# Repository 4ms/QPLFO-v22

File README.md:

#QPLFO v2.2
(also known as QPLFO v3)

This code runs on the STM32F030 version of the QPLFO, which is the factory-assembled version after March 2016. This code will not work on any kit versions of the QPLFO, nor any PCBs labeled version 1.x (green PCBs).

Note that one of the SWD programming pins is also used for the UI, so once the code has been flashed, it is difficult to re-flash it. The best technique I've found is to hit the reset button on the PCB at the right moment just before flashing.

This project was began using the [STM32F030x4 Application Template] (https://github.com/MrSpock/stm32f030x-gcc-template) from Martin Jurczuk, which is highly based on Mike Szczys [STM32F0-DISCOVERY template] (https://github.com/szczys/stm32f0-discovery-basic-template)

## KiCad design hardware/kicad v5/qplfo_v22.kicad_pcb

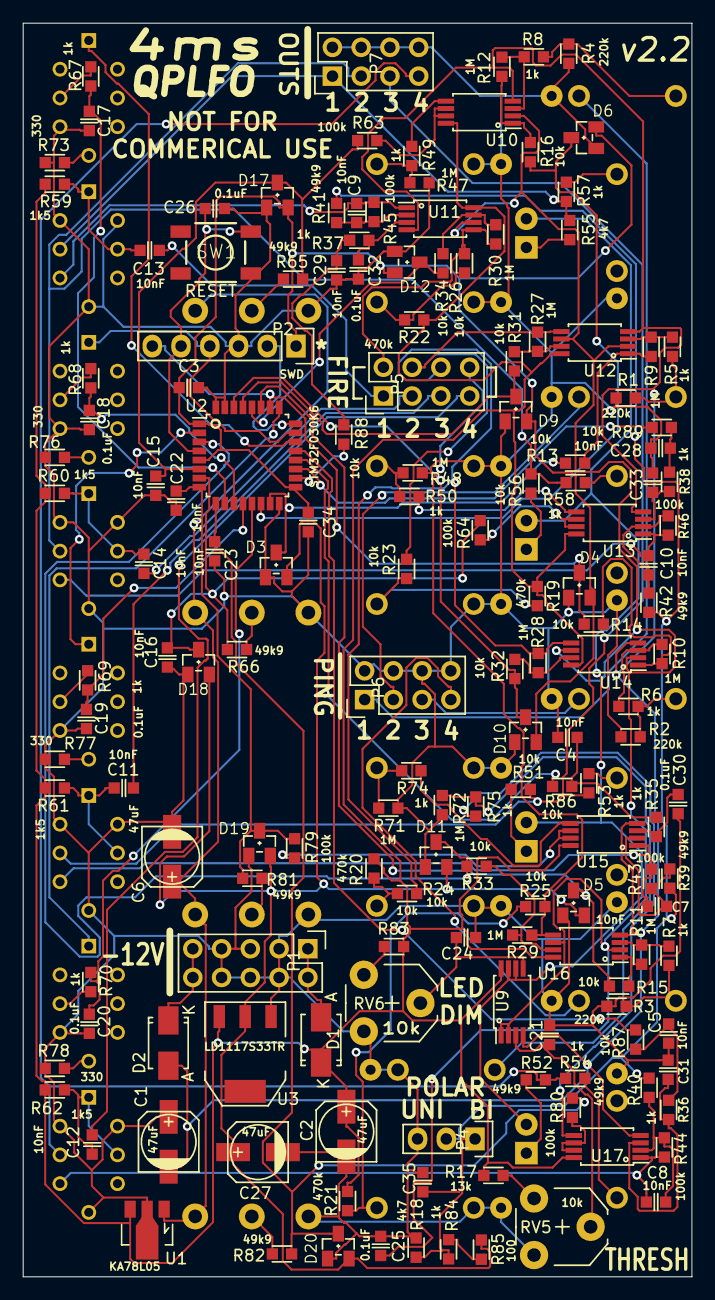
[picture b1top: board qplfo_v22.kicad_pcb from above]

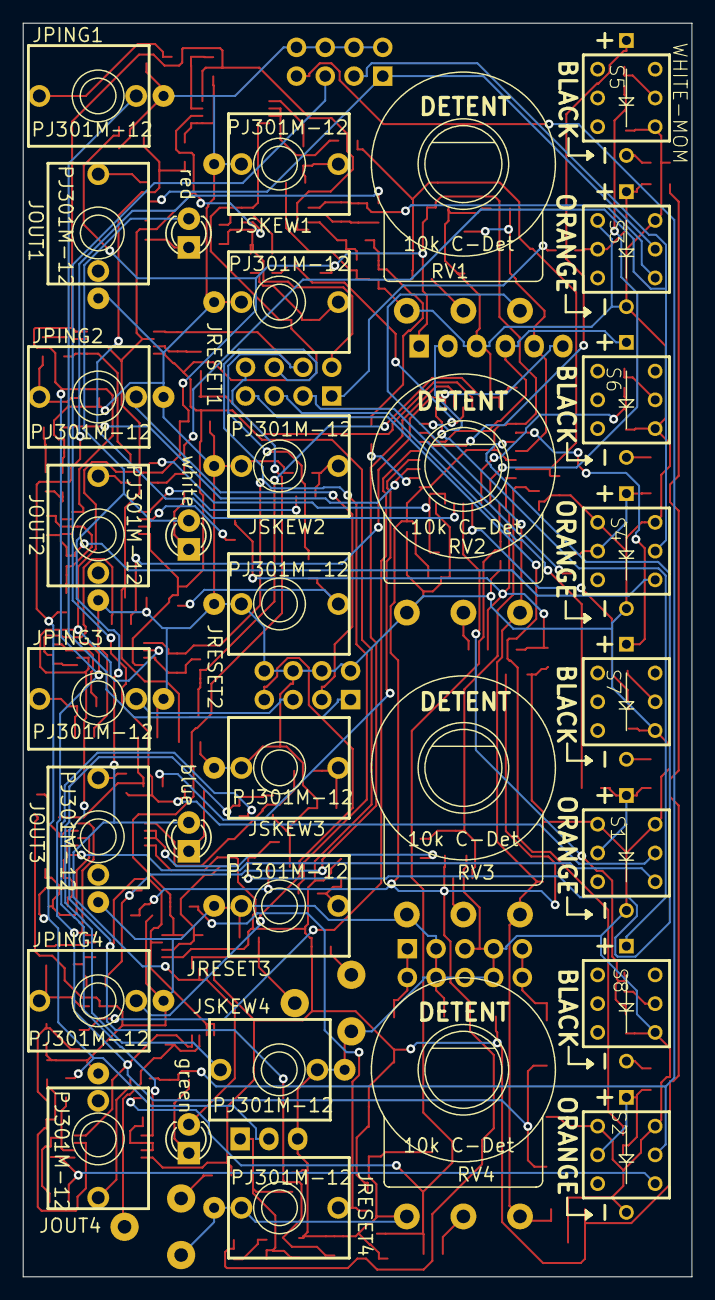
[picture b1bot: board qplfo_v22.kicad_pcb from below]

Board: 2 copper layers, 59.1 x 110.7 mm, 191 parts (32 on the bottom side), 130 nets.

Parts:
C1, C2, C6, C27: 47uF; c_elec_5x5.3
C3, C17, C18, C19, C20, C21, C24, C25, C26, C30, C31, C32, C33, C34, C35: 0.1uF; C0603
C4, C5, C7, C8, C9, C10, C11, C12, C13, C14, C15, C16, C22, C23, C28, C29: 10nF; C0603
D1, D2: B140; Diode-SMA_Standard
D3, D4, D5, D6, D9, D10, D11, D12, D17, D18, D19, D20: BAT54S; SOT23
D13: blue; LED-3MM-SQUARE-ANODE
D14: green; LED-3MM-SQUARE-ANODE
D15: red; LED-3MM-SQUARE-ANODE
D16: white; LED-3MM-SQUARE-ANODE
JOUT1, JOUT2, JOUT3, JOUT4: PJ301M-12; PJ301M-12-FIX
JPING1, JPING2, JPING3, JPING4: PJ301M-12; PJ301M-12-FIX
JRESET1, JRESET2, JRESET3, JRESET4: PJ301M-12; PJ301M-12-FIX
JSKEW1, JSKEW2, JSKEW3, JSKEW4: PJ301M-12; PJ301M-12-FIX
P1: CONN_02X05; Pin_Header_Straight_2x05
P2: SWD; Pin_Header_Straight_1x06
P4: HEADER-MALE-1X3-TH; Pin_Header_Straight_1x03
P5: FIRE; Pin_Header_Straight_2x04
P6: PINGS; Pin_Header_Straight_2x04
P7: OUTS; Pin_Header_Straight_2x04
R1, R2, R3, R4: 220k; R0603
R5, R6, R7, R8, R35, R36, R37, R38, R49, R50, R53, R54, R57, R58, R67, R68, R69, R70, R74, R75, R84: 1k; R0603
R9, R10, R11, R12, R27, R28, R29, R30, R47, R48, R71, R72: 1M; R0603
R13, R14, R15, R16, R23, R24, R25, R26, R31, R32, R33, R34, R51, R56, R83, R86, R87, R88, R89: 10k; R0603
R17: 13k; R0603
R18, R55: 4k7; R0603
R19, R20, R21, R22: 470k; R0603
R39, R40, R41, R42, R52, R65, R66, R81, R82: 49k9; R0603
R43, R44, R45, R46, R63, R64, R79, R80: 100k; R0603
R59, R60, R61, R62: 1k5; R0603
R73, R76, R77, R78: 330; R0603
R85: 100; R0603
RV1, RV2, RV3, RV4: 10k C-Det; 16MM-RV16AF-4A
RV5, RV6: 10k; Potentiometer_VishaySpectrol-Econtrim-Type36M
S1, S2, S3, S4: ORANGE-LAT; BUTTON-LED-PB61303
S5, S6, S7, S8: WHITE-MOM; BUTTON-LED-PB61303
SW1: RESET; BUTTON-TACT-SKQG
U1: KA78L05; SOT89-3_Housing
U2: STM32F030K6; LQFP-32_7x7mm_Pitch0.8mm
U3: LD1117S33TR; SOT-223
U9, U10, U11, U12, U13, U14, U15, U16, U17: TL082; TSSOP-8_4.4x3mm_Pitch0.65mm

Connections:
+3V3: C3.1, C27.1, C34.1, D3.2, D4.2, D5.2, D6.2, D9.2, D10.2, D11.2, D12.2, D17.2, D18.2, D19.2, D20.2, P2.1, R85.2, U2.1, U2.5, U2.17, U3.2
+12V: C2.1, D1.1, R17.2, R19.2, R20.2, R21.2, R22.2, R59.1, R60.1, R61.1, R62.1, R83.2, U1.3, U3.3, U9.8, U10.8, U11.8, U12.8, U13.8, U14.8, U15.8, U16.8, U17.8
-12V: C1.2, D2.2, U9.4, U10.4, U11.4, U12.4, U13.4, U14.4, U15.4, U16.4, U17.4
/NRST: C26.1, P2.5, SW1.2, U2.4
ENVRAW1: R88.2, U2.18
ENVRAW2: R89.2, U2.19
ENVRAW3: R86.2, U2.20
ENVRAW4: R87.2, U2.21
GND: C1.1, C2.2, C3.2, C4.1, C5.1, C6.2, C15.2, C16.2, C17.1, C18.1, C19.1, C20.1, C21.2, C22.2, C23.2, C24.2, C25.2, C26.2, C27.2, C28.1, C29.1, C30.1, C31.1, C32.1, C33.1, C34.2, C35.1, D3.1, D4.1, D5.1, D6.1, D9.1, D10.1, D11.1, D12.1, D17.1, D18.1, D19.1, D20.1, JOUT1.2, JOUT2.2, JOUT3.2, JOUT4.2, JPING1.2, JPING2.2, JPING3.2, JPING4.2, JRESET1.2, JRESET1.3, JRESET2.2, JRESET2.3, JRESET3.2, JRESET3.3, JRESET4.2, JRESET4.3, JSKEW1.2, JSKEW1.3, JSKEW2.2, JSKEW2.3, JSKEW3.2, JSKEW3.3, JSKEW4.2, JSKEW4.3, P1.3, P1.4, P1.5, P1.6, P1.7, P1.8, P2.3, P4.3, P6.2, P6.4, P6.6, P6.8, P7.2, P7.4, P7.6, P7.8, R1.2, R2.2, R3.2, R4.2, R18.2, R47.1, R48.1, R71.1, R72.1, R73.1, R76.1, R77.1, R78.1, RV1.1, RV2.1, RV3.1, RV4.1, RV5.3, RV6.3, S1.1, S1.4, S1.8, S2.1, S2.4, S2.8, S3.1, S3.4, S3.8, S4.1, S4.4, S4.8, S5.6, S6.6, S7.6, S8.6, SW1.1, U1.2, U2.16, U2.31, U2.32, U3.1
unnamed: C4.2, R35.2, R86.1
unnamed: C5.2, R36.2, R87.1
unnamed: C7.1, R43.1, S1.6, U15.1
unnamed: C7.2, R39.1, R43.2, U15.2
unnamed: C8.1, R44.1, S2.6, U17.1
unnamed: C8.2, R40.1, R44.2, U17.2
unnamed: C9.1, R45.1, S3.6, U11.1
unnamed: C9.2, R41.1, R45.2, U11.2
unnamed: C10.1, R46.1, S4.6, U13.1
unnamed: C10.2, R42.1, R46.2, U13.2
unnamed: C11.1, R61.2, S1.2, S1.7
unnamed: C12.1, R62.2, S2.2, S2.7
unnamed: C13.1, R59.2, S3.2, S3.7
unnamed: C14.1, R60.2, S4.2, S4.7
unnamed: C21.1, RV5.2, U9.3
unnamed: C24.1, RV6.2, U9.5
unnamed: C28.2, R38.2, R89.1
unnamed: C29.2, R37.2, R88.1
unnamed: C30.2, R35.1, U15.3
unnamed: C31.2, R36.1, U17.3
unnamed: C32.2, R37.1, U11.3
unnamed: C33.2, R38.1, U13.3
unnamed: C35.2, P4.1, R18.1, R84.1
unnamed: D1.2, P1.1, P1.2
unnamed: D2.1, P1.9, P1.10
unnamed: D13.2, R51.1
unnamed: D14.2, R52.1
unnamed: D15.2, R55.1
unnamed: D16.2, R56.1
unnamed: JOUT1.1, R57.1
unnamed: JOUT2.1, R58.1
unnamed: JOUT3.1, R53.1
unnamed: JOUT4.1, R54.1
unnamed: JPING1.1, R4.1, R8.2
unnamed: JPING2.1, R1.1, R5.2
unnamed: JPING3.1, R2.1, R6.2
unnamed: JPING4.1, R3.1, R7.2
unnamed: JRESET1.1, R22.1, R26.2
unnamed: JRESET2.1, R19.1, R23.2
unnamed: JRESET3.1, R20.1, R24.2
unnamed: JRESET4.1, R21.1, R25.2
unnamed: JSKEW1.1, R47.2, R49.2
unnamed: JSKEW2.1, R48.2, R50.2
unnamed: JSKEW3.1, R71.2, R74.2
unnamed: JSKEW4.1, R72.2, R75.2
unnamed: P2.2, U2.24
unnamed: R5.1, R9.2, U12.3
unnamed: R10.1, R14.1, U14.1
unnamed: R6.1, R10.2, U14.3
unnamed: R11.1, R15.1, U16.1
unnamed: R7.1, R11.2, U16.3
unnamed: R12.1, R16.1, U10.1
unnamed: R8.1, R12.2, U10.3
unnamed: R9.1, R13.1, U12.1
unnamed: R17.1, RV5.1
unnamed: R27.1, R31.1, U12.7
unnamed: R28.1, R32.1, U14.7
unnamed: R29.1, R33.1, U16.7
unnamed: R30.1, R34.1, U11.7
unnamed: R49.1, U10.5
unnamed: R50.1, U13.5
unnamed: R63.2, U10.6, U10.7
unnamed: R64.2, U13.6, U13.7
unnamed: R65.2, RV1.2
unnamed: R66.2, RV2.2
unnamed: R67.2, S5.5
unnamed: R68.2, S6.5
unnamed: R69.2, S7.5
unnamed: R70.2, S8.5
unnamed: R73.2, S5.8
unnamed: R74.1, U15.5
unnamed: R75.1, U17.5
unnamed: R76.2, S6.8
unnamed: R77.2, S7.8
unnamed: R78.2, S8.8
unnamed: R79.2, U15.6, U15.7
unnamed: R80.2, U17.6, U17.7
unnamed: R81.2, RV3.2
unnamed: R82.2, RV4.2
unnamed: R83.1, RV6.1
unnamed: R84.2, R85.1
OUT1J: P7.1, R55.2, R57.2, S3.5
OUT2J: P7.3, R56.2, R58.2, S4.5
OUT3J: P7.5, R51.2, R53.2, S1.5
OUT4J: P7.7, R52.2, R54.2, S2.5
PING1: D6.3, R16.2, U2.14
PING1SW: JPING1.3, P6.1
PING2: D3.3, R13.2, U2.15
PING2SW: JPING2.3, P6.3
PING3: D4.3, P2.6, R14.2, U2.26
PING3SW: JPING3.3, P6.5
PING4: D5.3, R15.2, U2.27
PING4SW: JPING4.3, P6.7
RESET1: D12.3, R34.2, U2.28
RESET2: D9.3, R31.2, U2.29
RESET3: D10.3, R32.2, U2.30
RESET4: D11.3, R33.2, U2.3
RESETMUTE1: C13.2, P5.1
RESETMUTE1B: P5.2, R26.1, R30.2, U11.5
RESETMUTE2: C14.2, P5.3
RESETMUTE2B: P5.4, R23.1, R27.2, U12.5
RESETMUTE3: C11.2, P5.5
RESETMUTE3B: P5.6, R24.1, R28.2, U14.5
RESETMUTE4: C12.2, P5.7
RESETMUTE4B: P5.8, R25.1, R29.2, U16.5
SKEW1-ADC: C15.1, D17.3, R63.1, R65.1, U2.6
SKEW2-ADC: C16.1, D18.3, R64.1, R66.1, U2.7
SKEW3-ADC: C22.1, D19.3, R79.1, R81.1, U2.8
SKEW4-ADC: C23.1, D20.3, R80.1, R82.1, U2.9
TAP1: C17.2, R67.1, U2.10
TAP2: C18.2, R68.1, U2.11
TAP3: C19.2, R69.1, U2.12
TAP4: C20.2, R70.1, U2.13
TAPLED1: S5.7, U2.22
TAPLED2: P2.4, S6.7, U2.23
TAPLED3: S7.7, U2.2
TAPLED4: S8.7, U2.25
VAA: C6.1, RV1.3, RV2.3, RV3.3, RV4.3, U1.1
VLED: D13.1, D14.1, D15.1, D16.1, U9.6, U9.7
Vpolar: P4.2, R39.2, R40.2, R41.2, R42.2
Vthresh: C25.1, U9.1, U9.2, U10.2, U11.6, U12.2, U12.6, U14.2, U14.6, U16.2, U16.6

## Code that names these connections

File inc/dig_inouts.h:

/*
 * dig_inouts.h
 */

#ifndef INOUTS_H_
#define INOUTS_H_

#include <stm32f0xx.h>

//INPUTS
//ADC: GPIOA GPIO_Pin_0 GPIO_Pin_1 GPIO_Pin_2 GPIO_Pin_3

//DEBUG_VERSION will disable the Tap Button LED for channel 2 (it's used by the SWD connection)
//#define DEBUG_VERSION
#define RELEASE_VERSION

#define TAPBUT_RCC RCC_AHBPeriph_GPIOA

#define TAPBUT_GPIO GPIOA
#define TAPBUT1_pin GPIO_Pin_4
#define TAPBUT1 (!(TAPBUT_GPIO->IDR & TAPBUT1_pin))
#define TAPBUT2_pin GPIO_Pin_5
#define TAPBUT2 (!(TAPBUT_GPIO->IDR & TAPBUT2_pin))
#define TAPBUT3_pin GPIO_Pin_6
#define TAPBUT3 (!(TAPBUT_GPIO->IDR & TAPBUT3_pin))
#define TAPBUT4_pin GPIO_Pin_7
#define TAPBUT4 (!(TAPBUT_GPIO->IDR & TAPBUT4_pin))

#define PING_RCC RCC_AHBPeriph_GPIOB
#define PING_GPIO GPIOB
#define PING1_pin GPIO_Pin_0
#define PING1 ((PING_GPIO->IDR & PING1_pin))
#define PING2_pin GPIO_Pin_1
#define PING2 ((PING_GPIO->IDR & PING2_pin))
#define PING3_pin GPIO_Pin_3
#define PING3 ((PING_GPIO->IDR & PING3_pin))
#define PING4_pin GPIO_Pin_4
#define PING4 ((PING_GPIO->IDR & PING4_pin))


#define RESET_RCC (RCC_AHBPeriph_GPIOB | RCC_AHBPeriph_GPIOF)

#define RESET123_GPIO GPIOB
#define RESET1_pin GPIO_Pin_5
#define RESET1 ((RESET123_GPIO->IDR & RESET1_pin))
#define RESET2_pin GPIO_Pin_6
#define RESET2 ((RESET123_GPIO->IDR & RESET2_pin))
#define RESET3_pin GPIO_Pin_7
#define RESET3 ((RESET123_GPIO->IDR & RESET3_pin))

#define RESET4_GPIO GPIOF
#define RESET4_pin GPIO_Pin_1
#define RESET4 ((RESET4_GPIO->IDR & RESET4_pin))


/*
#define EXTI_CLOCK_GPIO EXTI_PortSourceGPIOB
#define EXTI_CLOCK_pin EXTI_PinSource12
#define EXTI_CLOCK_line EXTI_Line12
#define EXTI_CLOCK_IRQ EXTI15_10_IRQn
*/


//OUTPUTS

#define TAPLED_RCC (RCC_AHBPeriph_GPIOA | RCC_AHBPeriph_GPIOF)
#define TAPLED1_GPIO GPIOA
#define TAPLED2_GPIO GPIOA
#define TAPLED3_GPIO GPIOF
#define TAPLED4_GPIO GPIOA

#define TAPLED1_pin GPIO_Pin_12
#define TAPLED2_pin GPIO_Pin_13
#define TAPLED3_pin GPIO_Pin_0
#define TAPLED4_pin GPIO_Pin_15

#define TAPLED1_ON TAPLED1_GPIO->BSRRL = TAPLED1_pin
#define TAPLED1_OFF TAPLED1_GPIO->BSRRH = TAPLED1_pin

#define TAPLED2_ON TAPLED2_GPIO->BSRRL = TAPLED2_pin
#define TAPLED2_OFF TAPLED2_GPIO->BSRRH = TAPLED2_pin

#define TAPLED3_ON TAPLED3_GPIO->BSRRL = TAPLED3_pin
#define TAPLED3_OFF TAPLED3_GPIO->BSRRH = TAPLED3_pin

#define TAPLED4_ON TAPLED4_GPIO->BSRRL = TAPLED4_pin
#define TAPLED4_OFF TAPLED4_GPIO->BSRRH = TAPLED4_pin


#define LFOPWM_GPIO_RCC RCC_AHBPeriph_GPIOA
#define LFOPWM_GPIO GPIOA
#define LFOPWM1_pin GPIO_Pin_8
#define LFOPWM2_pin GPIO_Pin_9
#define LFOPWM3_pin GPIO_Pin_10
#define LFOPWM4_pin GPIO_Pin_11

#define LFOPWM1_source GPIO_PinSource8
#define LFOPWM2_source GPIO_PinSource9
#define LFOPWM3_source GPIO_PinSource10
#define LFOPWM4_source GPIO_PinSource11

void init_dig_inouts(void);
void init_EXTI_inputs(void);
void init_inputread_timer(void);

void TAPLED_ON(uint8_t x);
void TAPLED_OFF(uint8_t x);
uint32_t TAPBUT(uint8_t x);
uint32_t PING(uint8_t x);
uint32_t RESETJACK(uint8_t x);

#endif /* INOUTS_H_ */

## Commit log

2014-09-06 repo init with working code and example
2014-09-06 StdPeriphLib Version info update
2016-03-01 Initial release for PCB 3.0
2016-10-05 First public commit, Updated license and README
2019-02-04 Added hardware files: kicad v4 and v5 projects, gerbers, and schematic PDF (in case you don't have kicad)
